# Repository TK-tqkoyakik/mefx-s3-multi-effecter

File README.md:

# マルチエフェクター製作プロジェクト

ESP32-S3を使った、ギター/ベース両対応のマルチエフェクター試作 v1 です。

## MEFX-S3 Desktopとは

MEFX-S3 Desktopは、Windowsで動く専用アプリです。実装済みの機能と、実機での確認が必要な項目を分けて開発しています。

このアプリでやりたいことは、かんたんに言うと次の6つです。

1. ESP32-S3のマルチエフェクターにつなぐ
2. ギター/ベース用の音色プリセットを作る
3. YouTubeの音を参考にして、近い音色を自動で考える
4. 作ったプリセットをアプリ内に保存する
5. PCに入れた音を、アプリ上でエフェクトをかけて試す
6. 音声ファイルをWAVへ変換したり、音声ファイルへエフェクトを書き出したりする

できるだけ外部の有料APIは使わず、PCの中で処理する方針です。

- OpenAI APIは使いません
- YouTube公式APIは使いません
- クラウド解析APIは使いません
- ffmpeg、Python、Demucsなどをアプリに同梱して、ローカルで解析します

YouTube音声の取得には通信が必要ですが、取得後の音源分離・解析はPC内で処理します。

## Windowsアプリ版の現在地

デスクトップアプリ版は `apps/desktop/` にあります。

今できている主な機能:

- Dashboard
- Manual Editor
- Tone Match
- Audio FX
- Audio Files
- Library
- Settings
- 日本語/英語の切り替え
- アプリ内プリセット保存
- シミュレーター
- ローカル解析サーバー内蔵
- ffmpeg/ffprobe同梱
- Python同梱
- yt-dlp/Demucs/PyTorch/Torchaudio同梱
- Demucsモデルキャッシュ同梱
- IR Library/WAV IR管理
- Audio FXでIRあり/なしの比較
- 音声ファイルのWAV変換
- 音声ファイルへのプリセットエフェクト書き出し
- 軽量トーン `deviceTone` の生成・PC側プレビュー（ESP32 v1には送信しない）
- Electron Web Bluetoothからの実機接続入口
- Windowsインストーラー生成

Audio FXでは、PCの入力音をアプリに入れて、プリセットの値で音を変えるモードを作っています。

Audio Filesでは、手元の音声ファイルを選んで、WAVへ変換したり、今のプリセットの音作りをファイルへ書き出したりできます。たとえば、録音済みのギター音やベース音にエフェクトをかけたWAVを作れます。

アプリ側の仕上げ確認は [Phase 40 仕上げ確認](docs/app/05_Phase40_仕上げ確認.md) にまとめています。

YouTube解析は仮サーバーだけの段階ではなく、yt-dlpで音声を取得し、Demucsで分離する処理を実装済みです。ギターは `other` ステム（ギター以外の楽器も含む）、ベースは `bass` ステムを解析します。Demucsが未準備・失敗の場合は、中高域/低域のフィルターによる簡易抽出へ切り替えます。完全なギター単独分離や原音色の再現を保証するものではありません。

ESP32 v1へ送る音作りの値は基本6エフェクトです。WAV IRや `deviceTone` はPC専用で、BLE送信には含めません。仕様は [BLE契約](shared/ble-contract.md) を参照してください。

基板と手はんだ用部品は到着済みです。現行の音声回路はCS4270構成で、PCM1808/PCM5102Aの別モジュール構成ではありません。まず1枚を部品面を上にして直配線で机上確認し、ケースへの組み込みは後回しにします。接続方法は [直配線接続表16](docs/hardware/16_直配線接続表.txt) と [R-78の向きと直配線図17](docs/hardware/17_R78向きと直配線図.txt) を優先し、4本足端子台は使いません。作業全体の流れは [初回実装手順14](docs/hardware/14_届いた部品_初回実装手順.txt) を参照してください。

ESP32開発ボード単体の書き込み・起動には [過去の確認記録](docs/firmware/01_ESP32-S3ファームウェア実機確認.txt) がありますが、CS4270とアナログ回路を含む音出し、BLE経由の一連の実機操作は未確認です。ローカルの自動検証とは区別します。

### 配布物と現在ソースの区別

既存の `output/desktop/01_別PC配布/MEFX-S3 Desktop Setup 0.1.0.exe` と [0.1.1](output/desktop/02_別PC配布/) は過去版です。現行0.1.2の個人試験用ZIPは [03_別PC配布](output/desktop/03_別PC配布/) にあります。NSIS生成に加えて、今回の展開版EXEの起動も、このPCのアプリケーション制御ポリシーで拒否されました。一般配布対応・別PC動作確認は未完了です。Windowsの保護設定を無効化せず、署名と全同梱物の確認を進める必要があります。

0.1.1では設定画面にプリセット・IR WAV・設定のバックアップ/復元、破損時の前回正常データへの復旧を追加しました。Tone Matchは進行段階・中止・抽出方式（Demucs、簡易フィルター、音源未解析のデモ）を表示します。実装・検証と追加作業は [実機なし改善記録08](docs/app/08_実機なし改善と追加調査.txt) にまとめています。

0.1.2では本体JSON検証、BLE接続先の明示許可、音声ファイル処理の中止、Python全依存・モデルのハッシュ固定、署名監査を追加しました。[接続と配布の安定化09](docs/app/09_接続と配布安定化.txt) に成功したテストと未確認項目を記録しています。本体向けビルドは成功していますが、COMポートが見つからないため書込・実BLE通信・実際の音出しは未試験です。

## GitHubでWindowsインストーラーを作る方法

GitHub Actions用のworkflowはローカルに用意されています。ただし、このワークスペースでは `apps/desktop/` と `.github/workflows/build-desktop-installer.yml` などがGit未追跡で、今回のローカル変更はActionsへ未反映です。ローカルにファイルがあることを、GitHub上で実行・成功した証拠にはしません。

以下は、対象ソースとworkflowがGitHubへ反映された後の手順です。本作業ではcommit/push/ブランチ作成は行いません。

使うworkflow:

```text
.github/workflows/build-desktop-installer.yml
```

手動で作る手順:

1. GitHubでこのリポジトリを開く
2. 上のメニューから `Actions` を開く
3. `Build Desktop Installer` を選ぶ
4. `Run workflow` を押す
5. `skip_demucs_warmup` は普通は `false` のままでよい
6. ビルドが終わるまで待つ
7. できあがった `mefx-s3-desktop-windows-installer` をダウンロードする

このインストーラーには、YouTube解析と音声ファイル変換で使う `ffmpeg` も同梱する前提です。GitHub Actionsでは、インストーラーを作る前に、ffmpegで短いテスト音をWAV変換できるか確認します。

未署名のテスト用インストーラーは、署名用ツールを使わない `package:installer:unsigned` で作ります。正式にコード署名する場合だけ、通常の `package:installer` を使います。

`skip_demucs_warmup` の意味:

- `false`: 高精度解析用のDemucsモデルも準備する。時間はかかるが、本番に近い
- `true`: モデル準備を飛ばす。テストビルドは速いが、初回解析で追加準備が必要になる可能性がある

今のworkflowは手動実行だけです。

理由は、まだアプリ調整中で、毎回自動で配布物を作る段階ではないためです。

配布するときは、開発用リポジトリとは別に、ダウンロードできる人を制限した配布用リポジトリを作る予定です。

注意:

- 初回ビルドはPython、Demucs、PyTorch、モデルを準備するので時間がかかります
- 完成物は大きめです。今の全部入り方針では展開後に約2GB前後を想定しています
- まだ正式なコード署名はしていません。Windowsの設定によっては警告やブロックが出る場合があります
- 署名つきの正式配布は、後のPhaseで整える予定です
- インストーラーはインストール先を選べる形式です

## まず見るファイル

到着済み基板の組立・机上確認:

まず見る画像資料: [基板とESP32の画像配線ガイド18](docs/hardware/18_基板とESP32_画像配線ガイド.html)。実物写真の目印、穴とGPIOの対応、3Dのソケット取り付け図をオフラインで表示します。現物のはんだ・導通・電圧の確認とは区別します。

今回の外付け配線: [外付け端子の配線図19](docs/hardware/19_外付け端子の配線図.html)。ESP32のみソケットへ挿し、楽器INPUT・アンプOUTPUT・DC電源・R-78・押しボタン・任意のマイクを線で接続する全体図と拡大図です。外付け端子の現物配置は導通確認が必要です。

1. [JLCPCB START HERE](JLCPCB_START_HERE.html)
2. [製造データの現行案内](docs/pcb-assembly/README.txt)
3. [基板表向き・ケース後回し手順](docs/hardware/10_基板表向き_ケース後回し手順.txt)
4. [届いた部品からの初回実装手順](docs/hardware/14_届いた部品_初回実装手順.txt)
5. [直配線接続表](docs/hardware/16_直配線接続表.txt)
6. [R-78の向きと直配線図](docs/hardware/17_R78向きと直配線図.txt)

最新製造データ07（再確認用。旧04/05/06は発注不可）:

- [07の注文設定・向き確認](docs/pcb-assembly/07_order_package/これをJLCPCBに送る.txt)
- [Gerber ZIP 07](docs/pcb-assembly/07_order_package/UPLOAD_THIS_GERBER_07.zip)
- [BOM CSV 07](docs/pcb-assembly/07_order_package/UPLOAD_THIS_BOM_07.csv)
- [CPL CSV 07](docs/pcb-assembly/07_order_package/UPLOAD_THIS_CPL_07.csv)
- [旧04版の履歴（発注不可）](docs/pcb-assembly/04_README.txt)

設計/実装資料:

- [作業手順書](docs/作業手順書.md)
- [必要なもの一覧](docs/必要なもの.md)
- [本体設計 最小構成](docs/hardware/本体設計_最小構成.txt)
- [本体回路図](docs/hardware/本体回路図.html)
- [必要パーツ 最小構成](docs/hardware/必要パーツ_最小構成.txt)
- [回路・基板の最終監査](docs/hardware/04_最終回路監査.txt)
- [KiCad正式プロジェクト](docs/kicad/mefx_s3.kicad_pro)
- [シミュレーションファイル](sim/README.md)
- [ESP32なしで確認する方法](docs/シミュレーター手順.md)
- [PC Bluetooth接続](docs/PC_Bluetooth接続.md)
- [ローカル解析ランチャー](docs/ローカル解析ランチャー.md)
- [セキュリティメモ](docs/セキュリティメモ.md)
- [完成判定チェックリスト](docs/checklists/end-to-end.md)
- [ESP-IDF導入メモ](docs/ESP-IDF導入.md)
- [Phase 40 仕上げ確認](docs/app/05_Phase40_仕上げ確認.md)

## 今できること

- Webアプリを起動できる
- YouTube音声の取得・Demucs分離・特徴量解析を行うローカルサーバーを起動できる
- ESP32が無くても、WebアプリのSimulatorボタンで動作確認できる
- 手動プリセット作成、保存、送信の流れを確認できる
- デスクトップアプリでは、手元の音声ファイルをWAV変換し、現在のプリセットをかけたWAVを書き出せる
- 到着済み部品を使い、基板表向き・直配線の手順で初回実装を進められる
- ケースSTLは参考資料として確認できる（組み込み・追加発注は机上確認後）

## JLCPCBの現在地

- 資料上の最新製造データは `07_order_package` です。基板・部品は到着済みで、現在は初回実装・机上確認の段階です。
- 保存済みの [07 DRC記録](docs/pcb-assembly/07_order_package/DRC_full_connection_recheck_07.txt) は違反0・未配線0、[07 ERC記録](docs/pcb-assembly/07_order_package/ERC_full_connection_recheck_07.txt) はエラー0・警告0です（2026-06-26時点。実機動作の保証ではありません）。
- [07全接続監査サマリー](docs/pcb-assembly/07_order_package/全接続監査サマリー_07.txt) は40ネット・206パッド・BOM内SMT 59点を記録しています。
- 再発注時も07のGerber/BOM/CPLを同一版で使用し、JLCPCBプレビューでU1/U2/U4のPin 1とD1の向きを再確認します。旧04/05/06は使用しません。
- ケースは後回しです。寸法データの検査と、現物の干渉・踏み込み強度の確認は別に扱います。

## すぐ使うコマンド

JLCPCB開始ページを開く:

```powershell
.\scripts\open-jlcpcb-start.ps1
```

環境チェック:

```powershell
.\scripts\check-env.ps1
```

解析サーバー起動:

```powershell
.\scripts\run-server.ps1
```

GitHub Pagesから使うローカル解析サーバーを手動起動:

```powershell
.\scripts\start-local-analyzer.cmd
```

Webアプリ起動:

```powershell
.\scripts\run-web.ps1
```

Webアプリのビルド確認:

```powershell
.\scripts\build-web.ps1
```

サーバーテスト:

```powershell
.\scripts\test-server.ps1
```

ESP32ファームウェアビルド:

```powershell
.\scripts\build-firmware.ps1
```

KiCadを開く:

```powershell
.\scripts\open-kicad.ps1
```

## 現在の注意点

- Node.js/npmはこのプロジェクト内の `tools/` にポータブル版をダウンロード済みです。
- ESP-IDFとKiCadはインストール/検出済みです。
- ESP32-S3向けファームウェアには過去のビルド・書き込み記録があります。今回の現在ソースのビルド結果とは別に扱います。
- ESP32本体が未接続でも、WebアプリのSimulatorで先に画面とデータの流れを確認できます。
- YouTube音色解析の実装と、実音源での分離品質・実機での音色再現の検証は別です。ローカルテストの成功だけで実機完成とは判定しません。
- 配布0.1.0は過去版です。現行0.1.1は02_別PC配布のZIPです。GitHub Actionsへの反映と別PC・実ESP32検証は未完了です。

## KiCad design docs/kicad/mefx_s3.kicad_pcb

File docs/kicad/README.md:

# KiCad 正式設計 04

KiCad 10以降で `mefx_s3.kicad_pro` を開いてください。

- `mefx_s3.kicad_sch`: 正式回路図。ERCエラー0、警告0。
- `mefx_s3.kicad_pcb`: 正式2層基板。DRC違反0、未配線0。
- `MEFX.pretty`: この設計で使うローカルフットプリント。
- `fp-lib-table`: ローカルフットプリントライブラリ設定。

JLCPCBへ送るデータはKiCadフォルダから直接選ばず、
`docs/pcb-assembly/04_order_package` の `UPLOAD_THIS_..._04` 3ファイルを使用します。

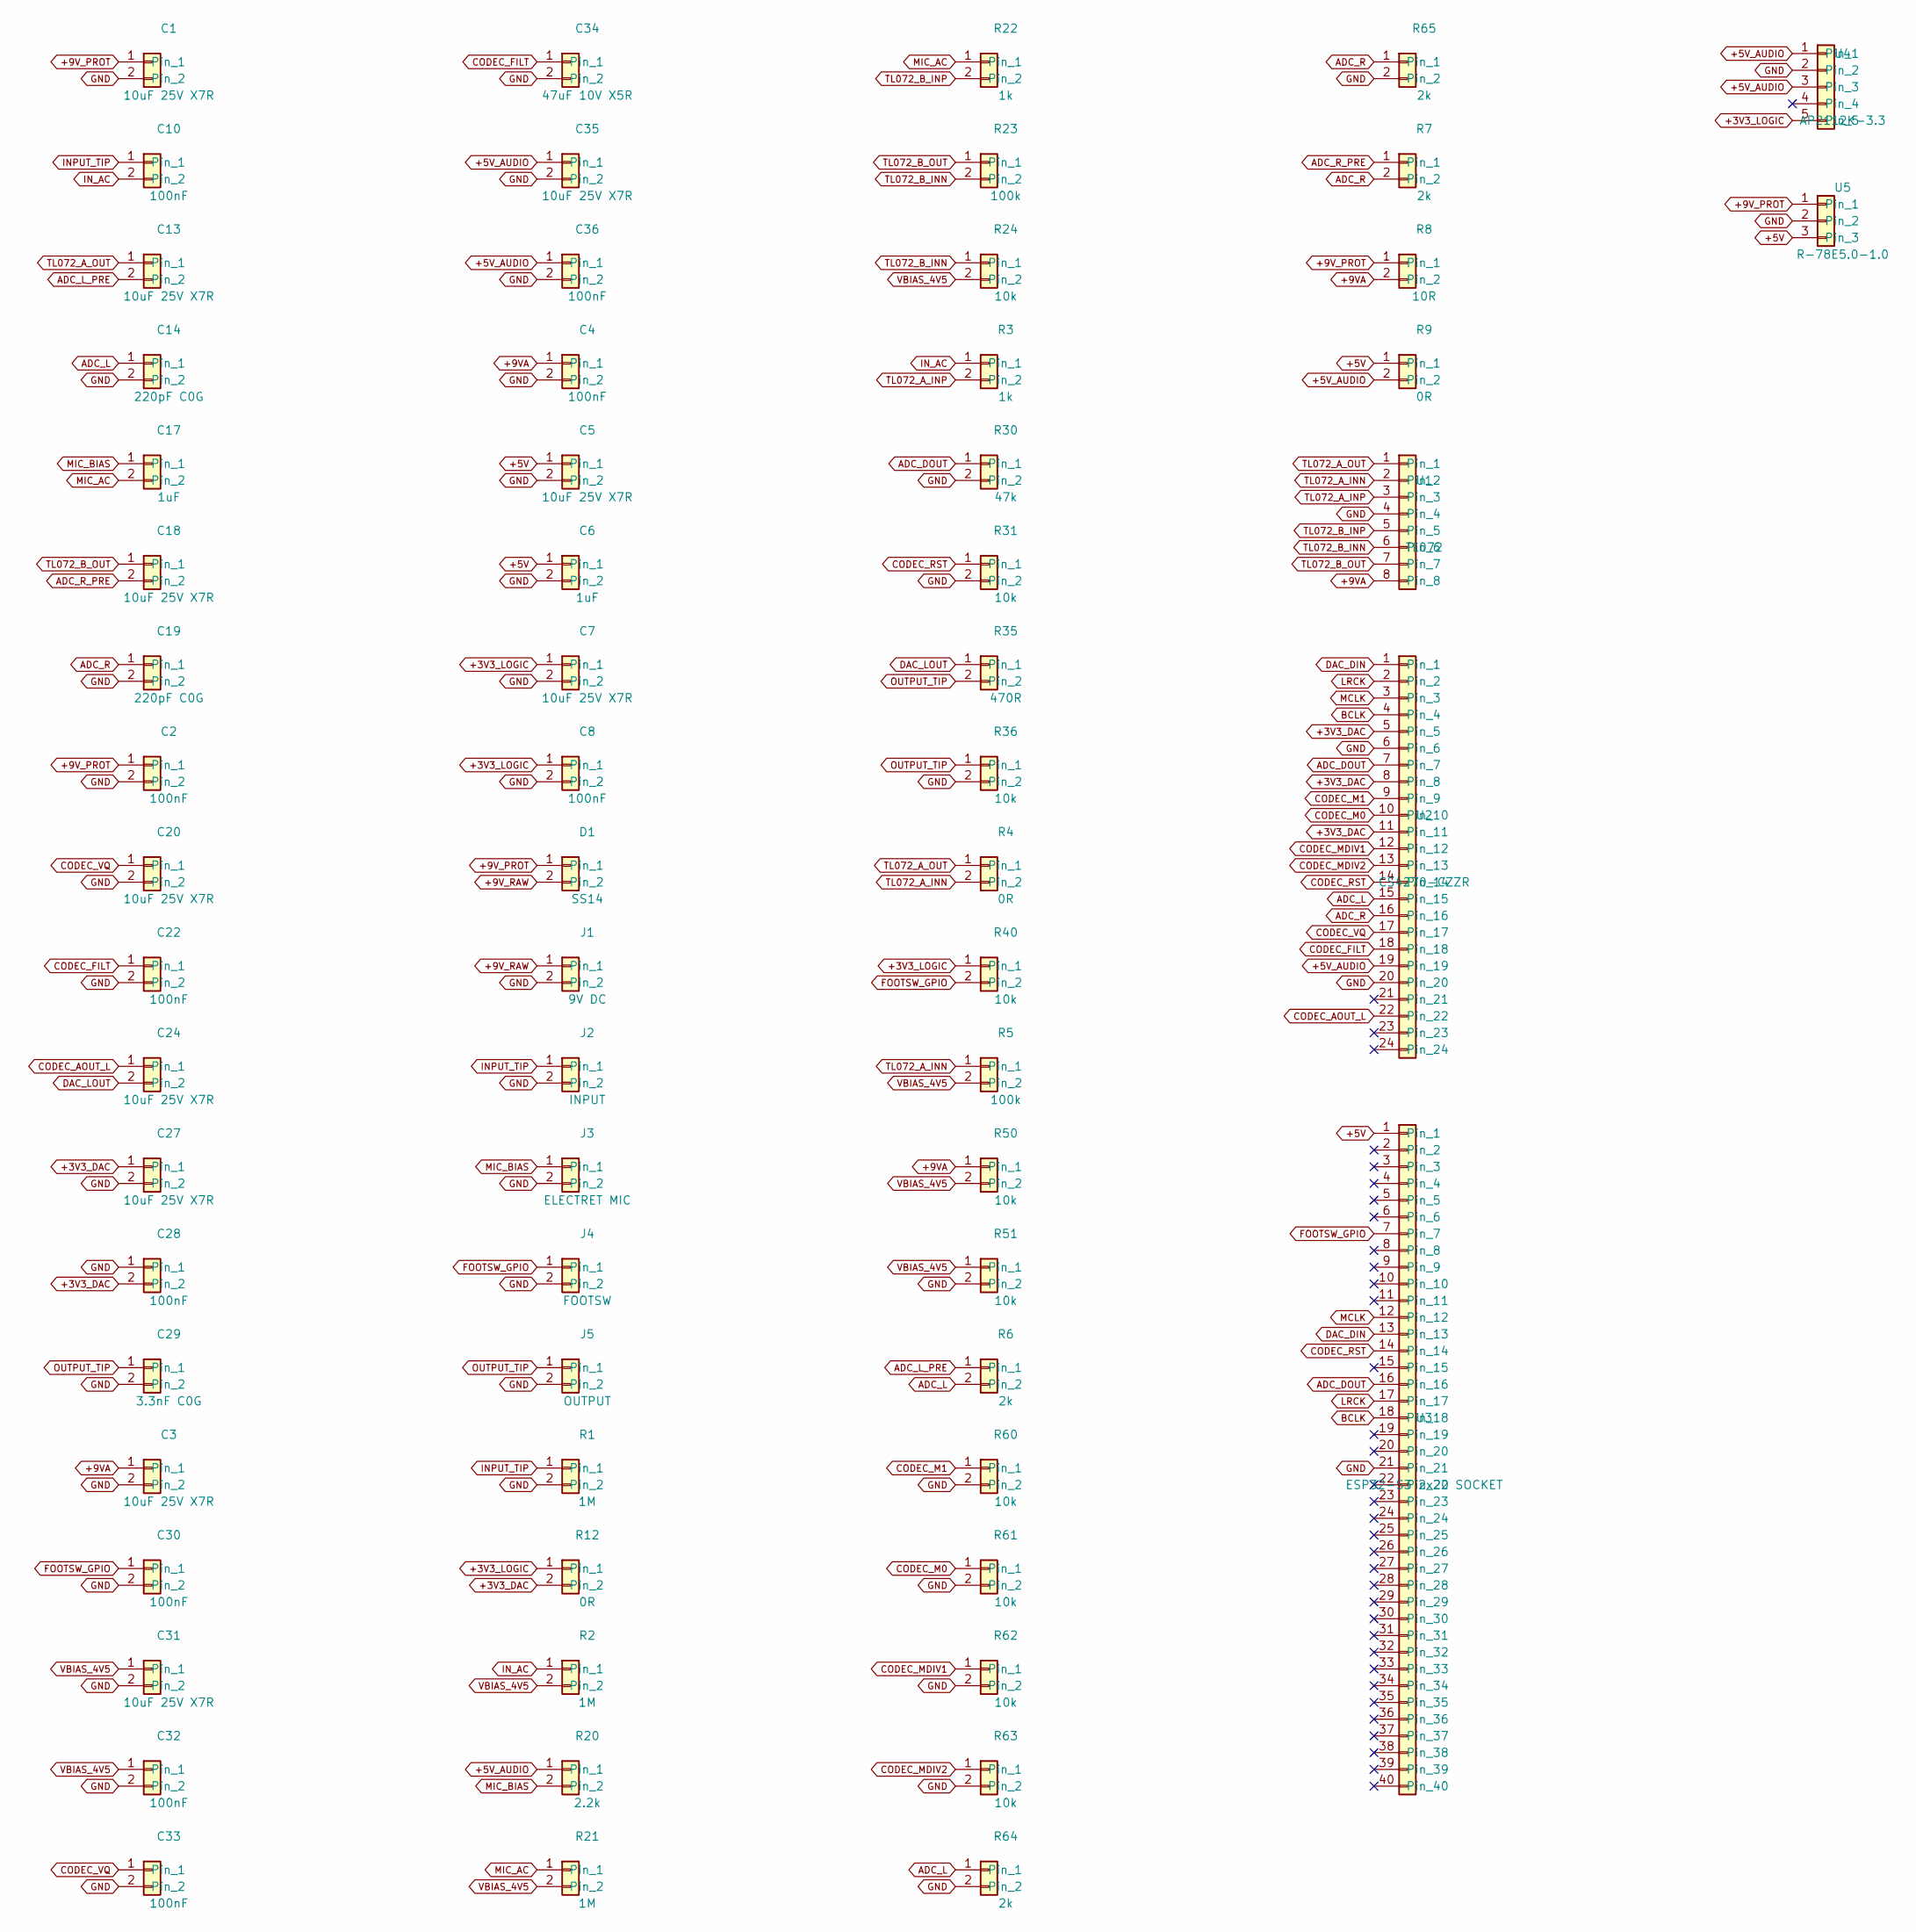
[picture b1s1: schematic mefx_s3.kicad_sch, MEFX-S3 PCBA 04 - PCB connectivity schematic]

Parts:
C1, C3, C5, C7, C13, C18, C20, C24, C27, C31, C35: 10uF 25V X7R
C2, C4, C8, C10, C22, C28, C30, C32, C33, C36: 100nF
C6, C17: 1uF
C14, C19: 220pF C0G
C29: 3.3nF C0G
C34: 47uF 10V X5R
D1: SS14
J1: 9V DC
J2: INPUT
J3: ELECTRET MIC
J4: FOOTSW
J5: OUTPUT
R1, R2, R21: 1M
R3, R22: 1k
R4, R9, R12: 0R
R5, R23: 100k
R6, R7, R64, R65: 2k
R8: 10R
R20: 2.2k
R24, R31, R36, R40, R50, R51, R60, R61, R62, R63: 10k
R30: 47k
R35: 470R
U1: TL072
U2: CS4270-CZZR
U3: ESP32-S3 2x20 SOCKET
U4: AP2112K-3.3; SOT-23-5
U5: R-78E5.0-1.0

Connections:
+3V3_DAC: C27.1, C28.2, R12.2, U2.5, U2.8, U2.11
+3V3_LOGIC: C7.1, C8.1, R12.1, R40.1, U4.5
+5V: C5.1, C6.1, R9.1, U3.1, U5.3
+5V_AUDIO: C35.1, C36.1, R9.2, R20.1, U2.19, U4.1, U4.3
+9VA: C3.1, C4.1, R8.2, R50.1, U1.8
+9V_PROT: C1.1, C2.1, D1.1 (K), R8.1, U5.1
+9V_RAW: D1.2 (A), J1.1
ADC_DOUT: R30.1, U2.7, U3.16
ADC_L: C14.1, R6.2, R64.1, U2.15
ADC_L_PRE: C13.2, R6.1
ADC_R: C19.1, R7.2, R65.1, U2.16
ADC_R_PRE: C18.2, R7.1
BCLK: U2.4, U3.18
CODEC_AOUT_L: C24.1, U2.22
CODEC_FILT: C22.1, C34.1, U2.18
CODEC_M0: R61.1, U2.10
CODEC_M1: R60.1, U2.9
CODEC_MDIV1: R62.1, U2.12
CODEC_MDIV2: R63.1, U2.13
CODEC_RST: R31.1, U2.14, U3.14
CODEC_VQ: C20.1, C33.1, U2.17
DAC_DIN: U2.1, U3.13
DAC_LOUT: C24.2, R35.1
FOOTSW_GPIO: C30.1, J4.1, R40.2, U3.7
GND: C1.2, C2.2, C3.2, C4.2, C5.2, C6.2, C7.2, C8.2, C14.2, C19.2, C20.2, C22.2, C27.2, C28.1, C29.2, C30.2, C31.2, C32.2, C33.2, C34.2, C35.2, C36.2, J1.2, J2.2, J3.2, J4.2, J5.2, R1.2, R30.2, R31.2, R36.2, R51.2, R60.2, R61.2, R62.2, R63.2, R64.2, R65.2, U1.4, U2.6, U2.20, U3.21, U4.2, U5.2
INPUT_TIP: C10.1, J2.1, R1.1
IN_AC: C10.2, R2.1, R3.1
LRCK: U2.2, U3.17
MCLK: U2.3, U3.12
MIC_AC: C17.2, R21.1, R22.1
MIC_BIAS: C17.1, J3.1, R20.2
OUTPUT_TIP: C29.1, J5.1, R35.2, R36.1
TL072_A_INN: R4.2, R5.1, U1.2
TL072_A_INP: R3.2, U1.3
TL072_A_OUT: C13.1, R4.1, U1.1
TL072_B_INN: R23.2, R24.1, U1.6
TL072_B_INP: R22.2, U1.5
TL072_B_OUT: C18.1, R23.1, U1.7
VBIAS_4V5: C31.1, C32.1, R2.2, R5.2, R21.2, R24.2, R50.2, R51.1

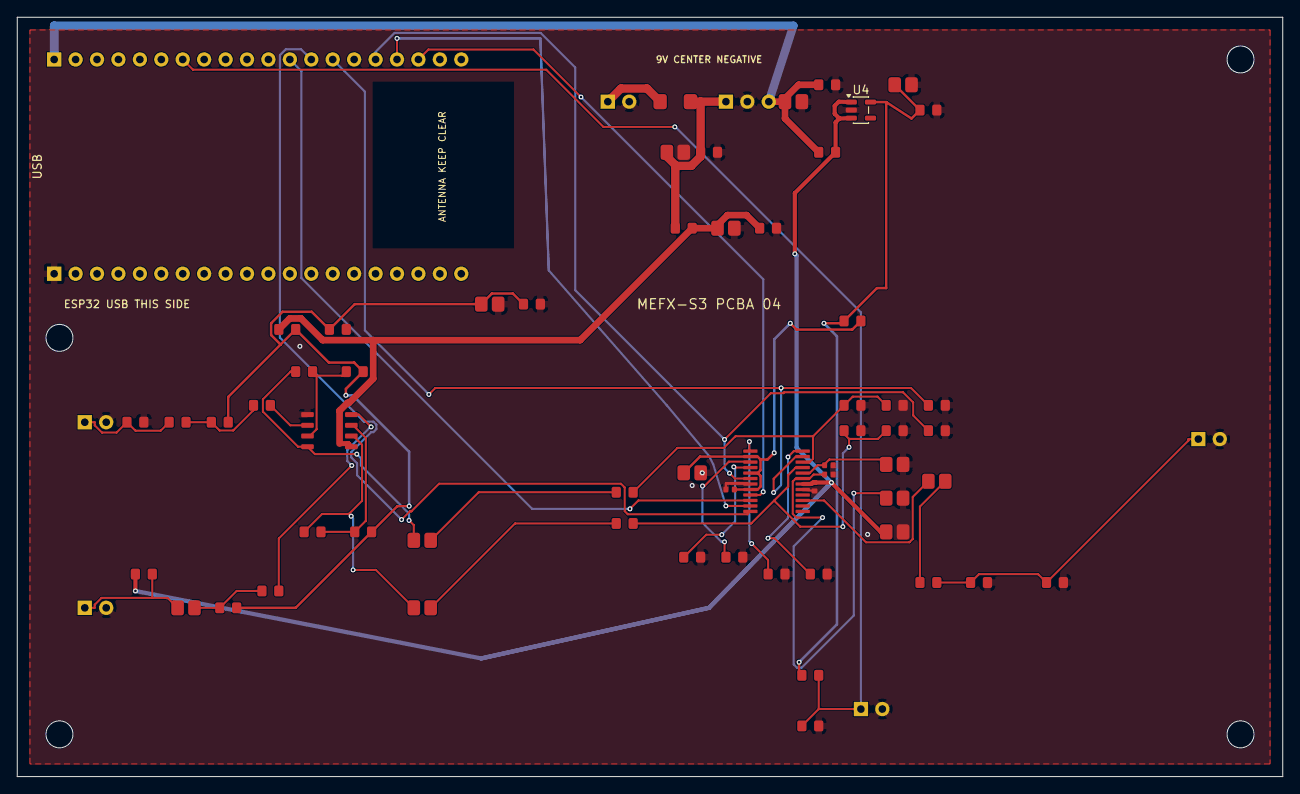
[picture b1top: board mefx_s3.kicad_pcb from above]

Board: 2 copper layers, 150.0 x 90.0 mm, 70 parts (0 on the bottom side), 39 nets.

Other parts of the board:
H1, H2, H3, H4: M3; MOUNT_M3

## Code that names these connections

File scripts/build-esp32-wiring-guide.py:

"""Read KiCad geometry and verify the wiring before rendering the offline guide."""
from __future__ import annotations

import argparse
import csv
import hashlib
import html
import json
import re
import shutil
from pathlib import Path

import pcbnew

ROOT = Path(__file__).resolve().parents[1]
OUT = ROOT / "docs/hardware/generated/esp32-wiring-guide"
PCB = ROOT / "docs/kicad/mefx_s3.kicad_pcb"
PHOTO = "board-photo.png"
ROW_A = "5V 14 13 12 11 10 9 46 3 8 18 17 16 15 7 6 5 4 EN 3V3".split()
ROW_B = "GND 19 20 21 47 48 45 0 35 36 37 38 39 40 41 42 2 1 RX TX".split()
SIGNALS = [
    ("power", 1, "+5V", "5V", "5V電源", "#bc3038", "基板 → ESP32", "I2Sではなく電源です。9V・3V3・GPIOへつながない。"),
    ("ground", 21, "GND", "GND", "共通GND", "#333333", "共通", "下列のUSB側から1穴目。電源OFFで基板GNDとの導通を確認。"),
    ("mclk", 12, "MCLK", "17", "基準クロック", "#176bc0", "ESP32 → U2", "ESP32の印字17へ。基板の穴番号12とGPIO17は別の番号。"),
    ("bclk", 18, "BCLK", "4", "ビットクロック", "#087e8b", "ESP32 → U2", "ESP32の印字4へ。穴番号4へつなぐという意味ではありません。"),
    ("lrck", 17, "LRCK", "5", "左右クロック", "#7858a6", "ESP32 → U2", "ESP32の印字5へ。BCLKとは別の信号。"),
    ("adc", 16, "ADC_DOUT", "6", "録音側の音声", "#197b58", "U2 → ESP32", "CS4270からESP32へ入る音声データ。"),
    ("dac", 13, "DAC_DIN", "16", "再生側の音声", "#b25b12", "ESP32 → U2", "ESP32からCS4270へ出す音声データ。ADC側と交換しない。"),
    ("reset", 14, "CODEC_RST", "15", "コーデックRESET", "#a33e81", "ESP32 → U2", "印字15へ。ESP32自身のEN端子には接続しない。"),
    ("switch", 7, "FOOTSW_GPIO", "9", "押しボタン", "#7d6b16", "J4 → ESP32", "外付けボタンはJ4へ。U3ではGPIO9へつながっています。"),
]


def mm(value):
    return round(float(pcbnew.ToMM(value)), 5)


def point(value):
    return [mm(value.x), mm(value.y)]


def esc(value):
    return html.escape(str(value), quote=True)


def main():
    parser = argparse.ArgumentParser()
    parser.add_argument("--photo", type=Path)
    args = parser.parse_args()
    OUT.mkdir(parents=True, exist_ok=True)
    board = pcbnew.LoadBoard(str(PCB))
    fps = {fp.GetReference(): fp for fp in board.GetFootprints()}
    u3 = {int(pad.GetNumber()): pad for pad in fps["U3"].Pads()}
    assert len(u3) == 40
    assert fps["U3"].GetOrientationDegrees() == 0
    for number, pad in u3.items():
        assert point(pad.GetPosition()) == [round(4.37 + ((number - 1) % 20) * 2.54, 5), 5.0 if number <= 20 else 30.4]
    external_nets = {"U5": ["+9V_PROT", "GND", "+5V"], "J1": ["+9V_RAW", "GND"],
                     "J2": ["INPUT_TIP", "GND"], "J3": ["MIC_BIAS", "GND"],
                     "J4": ["FOOTSW_GPIO", "GND"], "J5": ["OUTPUT_TIP", "GND"]}
    for ref, nets in external_nets.items():
        actual = {int(p.GetNumber()): p.GetNetname() for p in fps[ref].Pads()}
        assert [actual[i] for i in range(1, len(nets) + 1)] == nets, ref
    firmware = (ROOT / "firmware/components/audio_io/audio_io.c").read_text(encoding="utf-8")
    switch = (ROOT / "firmware/components/switch_control/switch_control.c").read_text(encoding="utf-8")
    macros = dict(re.findall(r"#define\s+(\w+)\s+GPIO_NUM_(\d+)", firmware + "\n" + switch))
    expected = {"I2S_MCLK": "17", "I2S_ADC_BCLK": "4", "I2S_ADC_WS": "5", "I2S_ADC_DIN": "6", "I2S_DAC_DOUT": "16", "CODEC_RESET": "15"}
    for key, gpio in expected.items():
        assert macros.get(key) == gpio, (key, macros.get(key))
    assert "GPIO_NUM_9" in switch
    with (ROOT / "docs/pcb-assembly/07_order_package/全パッド接続一覧_07.csv").open(encoding="utf-8-sig", newline="") as f:
        audit = {int(row["Pad"]): row["Net"] for row in csv.DictReader(f) if row["Reference"] == "U3"}
    signals = []
    for sid, pad, net, label, title, color, direction, note in SIGNALS:
        assert u3[pad].GetNetname() == net, (pad, net)
        assert audit[pad] == net, ("07 CSV differs", pad)
        assert (ROW_A + ROW_B)[pad - 1] == label
        signals.append(dict(id=sid, pad=pad, net=net, label=label, title=title, color=color,
                            direction=direction, note=note, pos=point(u3[pad].GetPosition()),
                            row="上列" if pad <= 20 else "下列", ordinal=(pad - 1) % 20 + 1))
    assert {n for n, p in u3.items() if p.GetNetname()} == {s[1] for s in SIGNALS}
    assert not u3[20].GetNetname(), "ESP32 3V3 must remain unconnected"
    pads = []
    parts = []
    for ref, fp in fps.items():
        parts.append(dict(ref=ref, value=fp.GetValue(), pos=point(fp.GetPosition()), rotation=fp.GetOrientationDegrees()))
        for pad in fp.Pads():
            pads.append(dict(ref=ref, number=pad.GetNumber(), net=pad.GetNetname(), pos=point(pad.GetPosition()),
                             size=point(pad.GetSize()), drill=point(pad.GetDrillSize()),
                             rotation=pad.GetOrientationDegrees(), rect=pad.GetShape() == pcbnew.PAD_SHAPE_RECT))
    tracks = []
    for track in board.GetTracks():
        if isinstance(track, pcbnew.PCB_TRACK) and not isinstance(track, pcbnew.PCB_VIA) and track.GetLayer() == pcbnew.F_Cu:
            tracks.append(dict(start=point(track.GetStart()), end=point(track.GetEnd()), width=mm(track.GetWidth())))
    if args.photo:
        shutil.copyfile(args.photo, OUT / PHOTO)
    assert (OUT / PHOTO).exists(), "Supply the user's physical-board photograph with --photo"
    payload = dict(width=150, height=90, pads=pads, parts=parts, tracks=tracks, signals=signals,
                   rows=[ROW_A, ROW_B], photo=PHOTO, pcbSha256=hashlib.sha256(PCB.read_bytes()).hexdigest(),
                   source="docs/kicad/mefx_s3.kicad_pcb", revision="07_order_package",
                   pinoutUrl="https://github.com/Freenove/Freenove_ESP32_S3_WROOM_Board_Lite/blob/main/ESP32S3_Lite_Pinout.png")
    serialized = json.dumps(payload, ensure_ascii=False, separators=(",", ":"))
    (OUT / "wiring-data.js").write_text("window.MEFX_WIRING_DATA=" + serialized + ";\n", encoding="utf-8")
    template = (ROOT / "docs/hardware/wiring-viewer/index.html").read_text(encoding="utf-8")
    guide = ROOT / "docs/hardware/18_基板とESP32_画像配線ガイド.html"
    guide.write_text(template, encoding="utf-8")
    report = ["MEFX-S3 画像配線ガイド 検証記録", "", "基板・07接続CSV・現行ファームウェアを照合。9接続すべて一致。",
              "U3: 40パッド、2.54mmピッチ、列間25.4mm、表面、USB左。",
              "U3-20 (ESP32 3V3) は未接続。U4の3.3V出力と追加接続しない。",
              "基板SHA256: " + payload["pcbSha256"], "", "接続:"]
    report.extend(f"U3-{s['pad']} / {s['net']} -> ESP32 {s['label']} ({s['row']} USB側から{s['ordinal']}穴目)" for s in signals)
    report.extend(["", "実物写真で確認した範囲: USB左、アンテナ右、端子印字が設計の並びと整合。",
                   "未確認: 裏面のはんだ、ソケットへの挿入、導通、電圧、起動、音出し。",
                   "3Dは取り付け説明用の簡略モデル。ソケット高さ・外形の実測や干渉保証ではない。",
                   "USB給電だけで完成回路を駆動する案内ではない。書込み時は基板からESP32を外す。"])
    (OUT / "検証記録.txt").write_text("\n".join(report) + "\n", encoding="utf-8")
    print(guide)
    print("PASS: 40 pads / 9 connections / firmware GPIO / audit CSV / 3V3 isolation")


if __name__ == "__main__":
    main()
